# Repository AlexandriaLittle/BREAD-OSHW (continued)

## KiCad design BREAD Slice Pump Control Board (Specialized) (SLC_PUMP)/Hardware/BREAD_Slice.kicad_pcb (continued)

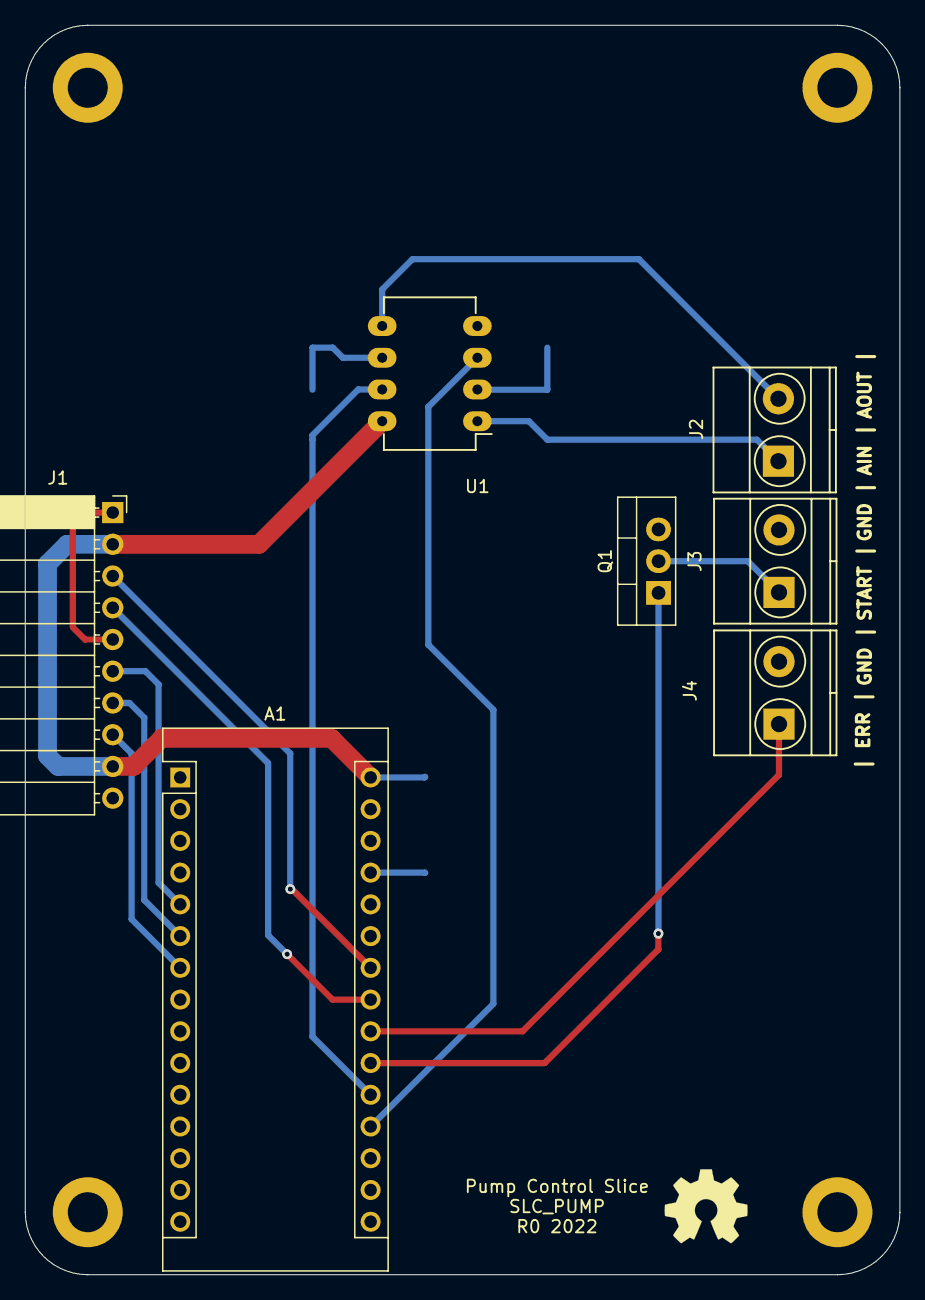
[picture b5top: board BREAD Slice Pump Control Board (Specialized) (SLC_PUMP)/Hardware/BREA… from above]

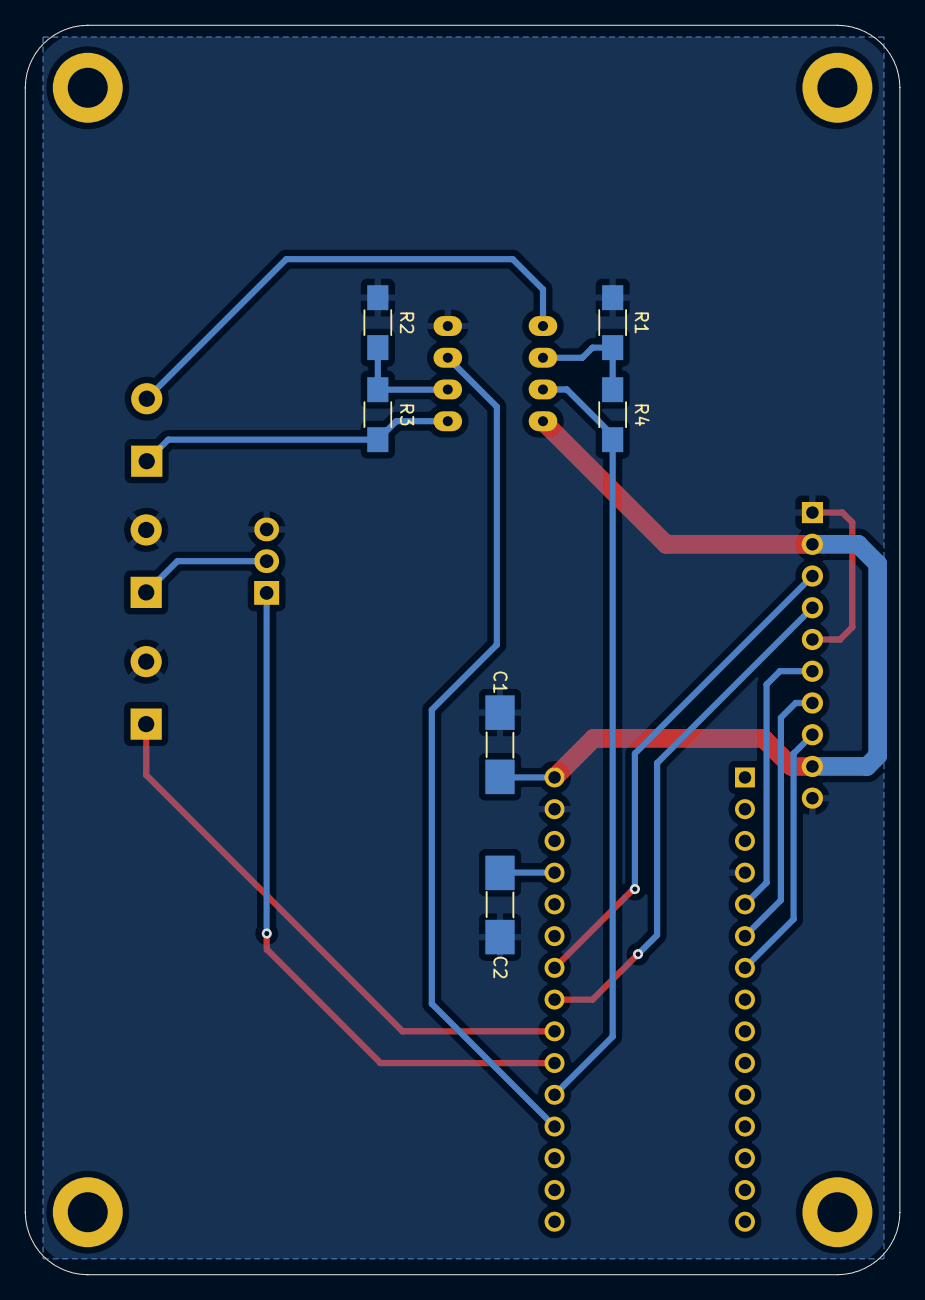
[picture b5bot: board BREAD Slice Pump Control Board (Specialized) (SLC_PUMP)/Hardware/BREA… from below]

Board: 2 copper layers, 70.0 x 100.0 mm, 18 parts (6 on the bottom side), 17 nets.

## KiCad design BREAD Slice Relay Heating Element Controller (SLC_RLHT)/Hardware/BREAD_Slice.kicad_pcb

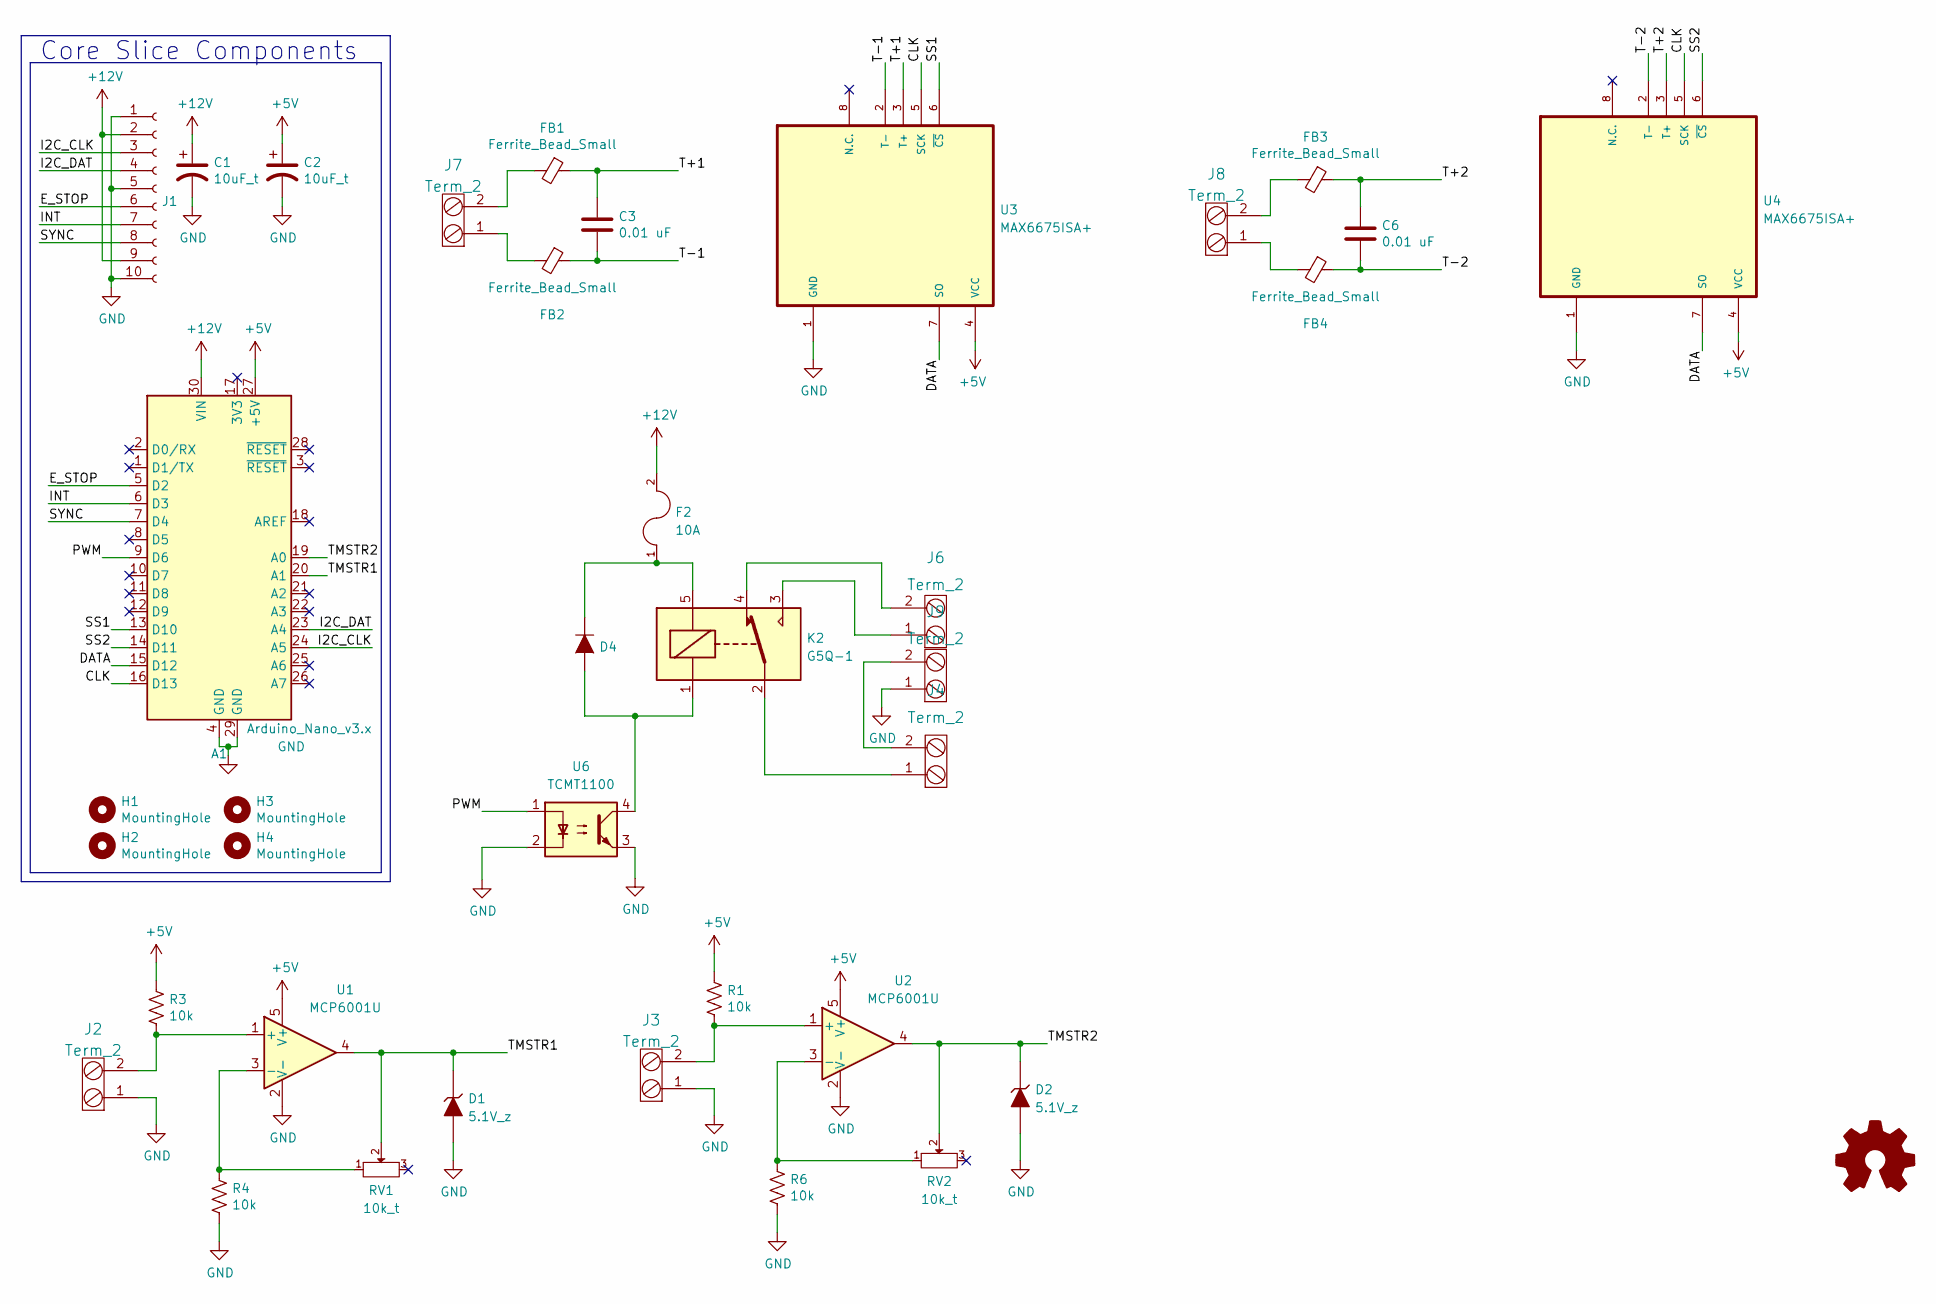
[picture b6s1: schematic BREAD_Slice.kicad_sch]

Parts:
A1: Arduino_Nano_v3.x; Arduino_Nano
C1, C2: 10uF_t; C_1206_3216Metric; Part # T491C106K025AT
C3, C6: 0.01 uF; C_1206_3216Metric
D1, D2: 5.1V_z; Diode_DO-41_SOD81_Horizontal_RM10; Part # 1N4733ATR
D4: General_Purpose_Diode; D_DO-201AD_P12.70mm_Horizontal; Part # 1N914BWS
F2: 10A; Fuse_Holder; Part # 3522-2
FB1, FB2, FB3, FB4: Ferrite_Bead_Small; R_1206_3216Metric
H1, H2, H3, H4: MountingHole; MountingHole_3.2mm_M3_DIN965_Pad
J1: Conn_01x10_Female; PinSocket_1x10_P2.54mm_Horizontal
J2, J3, J4, J6, J7, J8, J9: Term_2; TerminalBlock_Phoenix_MKDS-1,5-2_1x02_P5.00mm_Horizontal; Part # 1935161
K2: G5Q-1; Relay_SPDT_Omron-G5Q-1
Logo1: Logo_Open_Hardware_Small; OSHW-Symbol_6.7x6mm_SilkScreen
R1, R3, R4, R6: 10k; R_1206_HandSoldering
RV1, RV2: 10k_t; Potentiometer_Bourns_3296W_3-8Zoll_Inline_ScrewUp; Part # 1-1623849-0
U1, U2: MCP6001U; SOT-23-5
U3, U4: MAX6675ISA+; SOIC127P600X175-8N
U6: TCMT1100; SOP-4_4.4x2.6mm_P1.27mm

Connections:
+5V: A1.27 (+5V), C2.1, R1.1, R3.1, U1.5 (V+), U2.5 (V+), U3.4 (VCC), U4.4 (VCC)
+12V: A1.30 (VIN), C1.1, F2.2, J1.2, J1.9; also elsewhere on the board
/CLK: A1.16 (D13), U3.5 (SCK), U4.5 (SCK)
/DATA: A1.15 (D12), U3.7 (SO), U4.7 (SO)
/E_STOP: A1.5 (D2), J1.6
/I2C_CLK: A1.24 (A5), J1.3
/I2C_DAT: A1.23 (A4), J1.4
/INT: A1.6 (D3), J1.7
/PWM: A1.9 (D6), U6.1
/SS1: A1.13 (D10), U3.6 (~CS)
/SS2: A1.14 (D11), U4.6 (~CS)
/SYNC: A1.7 (D4), J1.8
/T+1: C3.1, FB1.1, U3.3 (T+)
/T+2: C6.1, FB3.1, U4.3 (T+)
/T-1: C3.2, FB2.1, U3.2 (T-)
/T-2: C6.2, FB4.1, U4.2 (T-)
/TMSTR1: A1.20 (A1), D1.1 (K), RV1.2, U1.4
/TMSTR2: A1.19 (A0), D2.1 (K), RV2.2, U2.4
GND: A1.4 (GND), A1.29 (GND), C1.2, C2.2, D1.2 (A), D2.2 (A), J1.1, J1.5, J1.10, J2.1, J3.1, J9.1, R4.2, R6.2, U1.2 (V-), U2.2 (V-), U3.1 (GND), U4.1 (GND), U6.2, U6.3
unnamed: D4.1 (K), F2.1, K2.5
unnamed: D4.2 (A), K2.1, U6.4
unnamed: FB1.2, J7.2
unnamed: FB2.2, J7.1
unnamed: FB3.2, J8.2
unnamed: FB4.2, J8.1
unnamed: J2.2, R3.2, U1.1 (+)
unnamed: J3.2, R1.2, U2.1 (+)
unnamed: J4.1, K2.2
unnamed: J6.1, K2.3
unnamed: J6.2, K2.4
unnamed: J4.2, J9.2
unnamed: R4.1, RV1.1, U1.3 (-)
unnamed: R6.1, RV2.1, U2.3 (-)

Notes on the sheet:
Core Slice Components

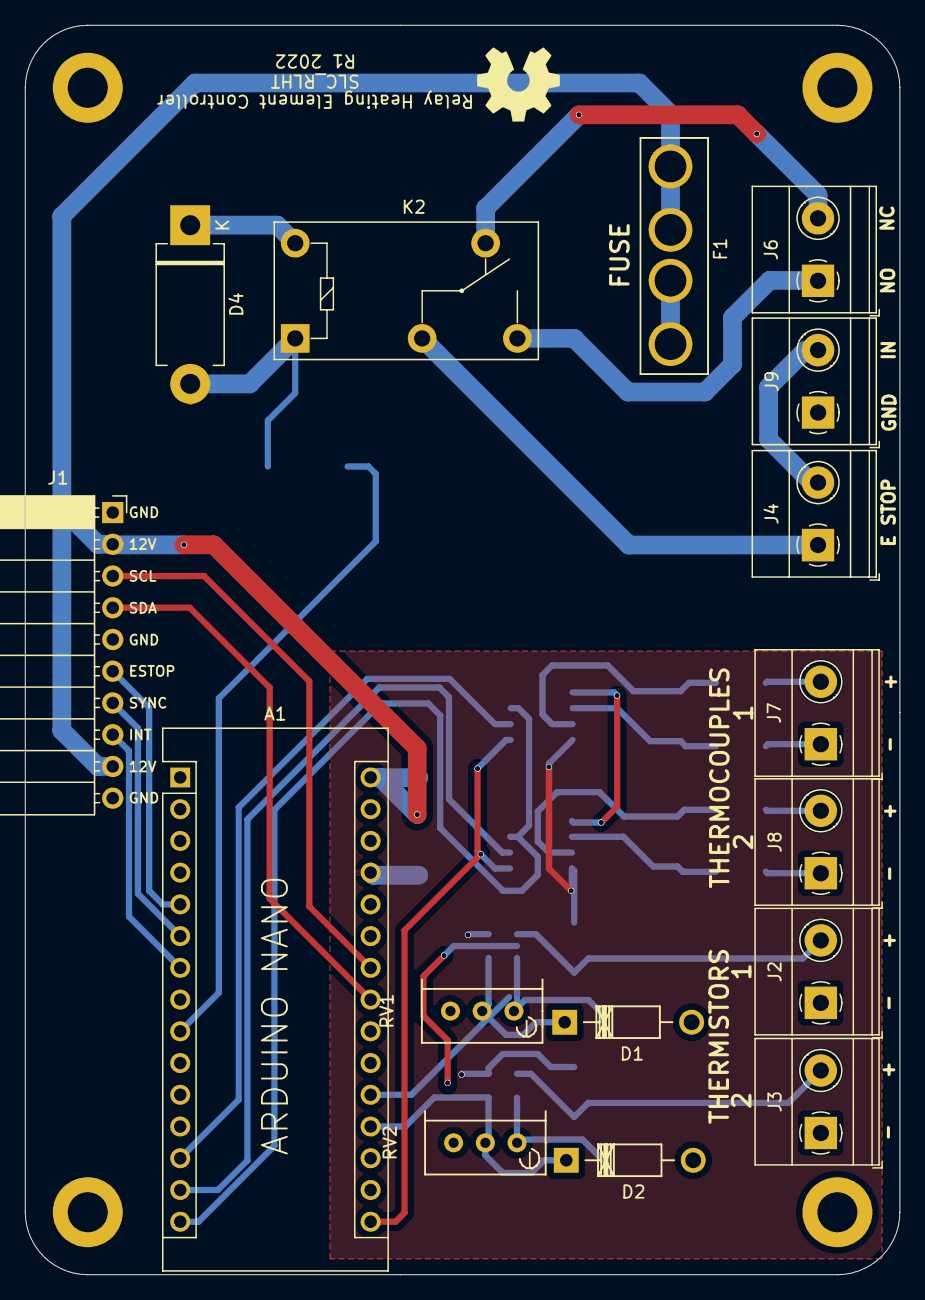
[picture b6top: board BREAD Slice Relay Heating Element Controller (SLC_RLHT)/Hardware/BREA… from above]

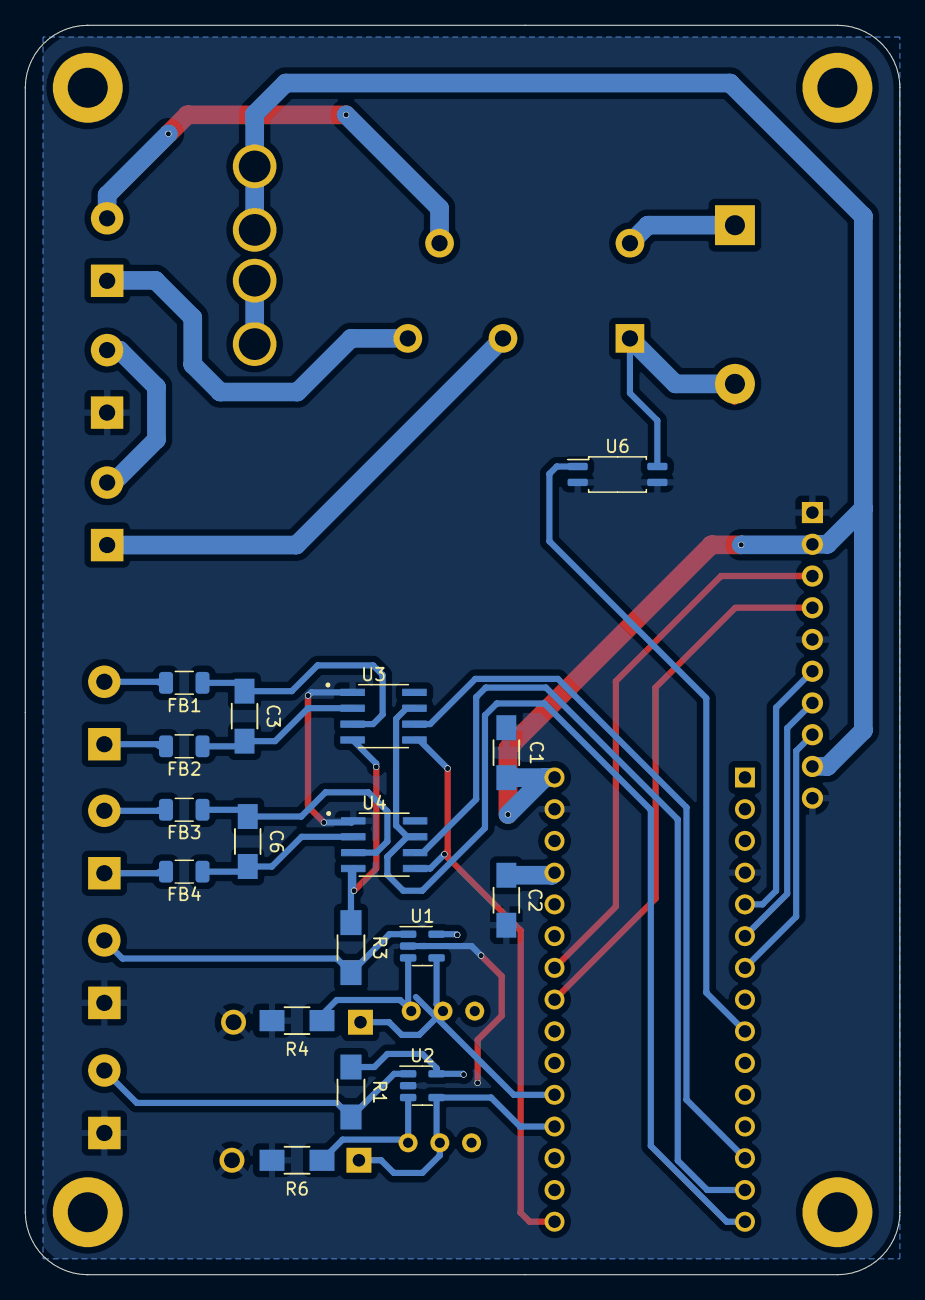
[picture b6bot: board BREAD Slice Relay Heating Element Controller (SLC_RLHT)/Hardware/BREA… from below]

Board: 2 copper layers, 70.0 x 100.0 mm, 38 parts (17 on the bottom side), 33 nets.

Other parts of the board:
F1: 10A; Fuse_Holder

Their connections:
+12V: F1.2; also elsewhere on the board

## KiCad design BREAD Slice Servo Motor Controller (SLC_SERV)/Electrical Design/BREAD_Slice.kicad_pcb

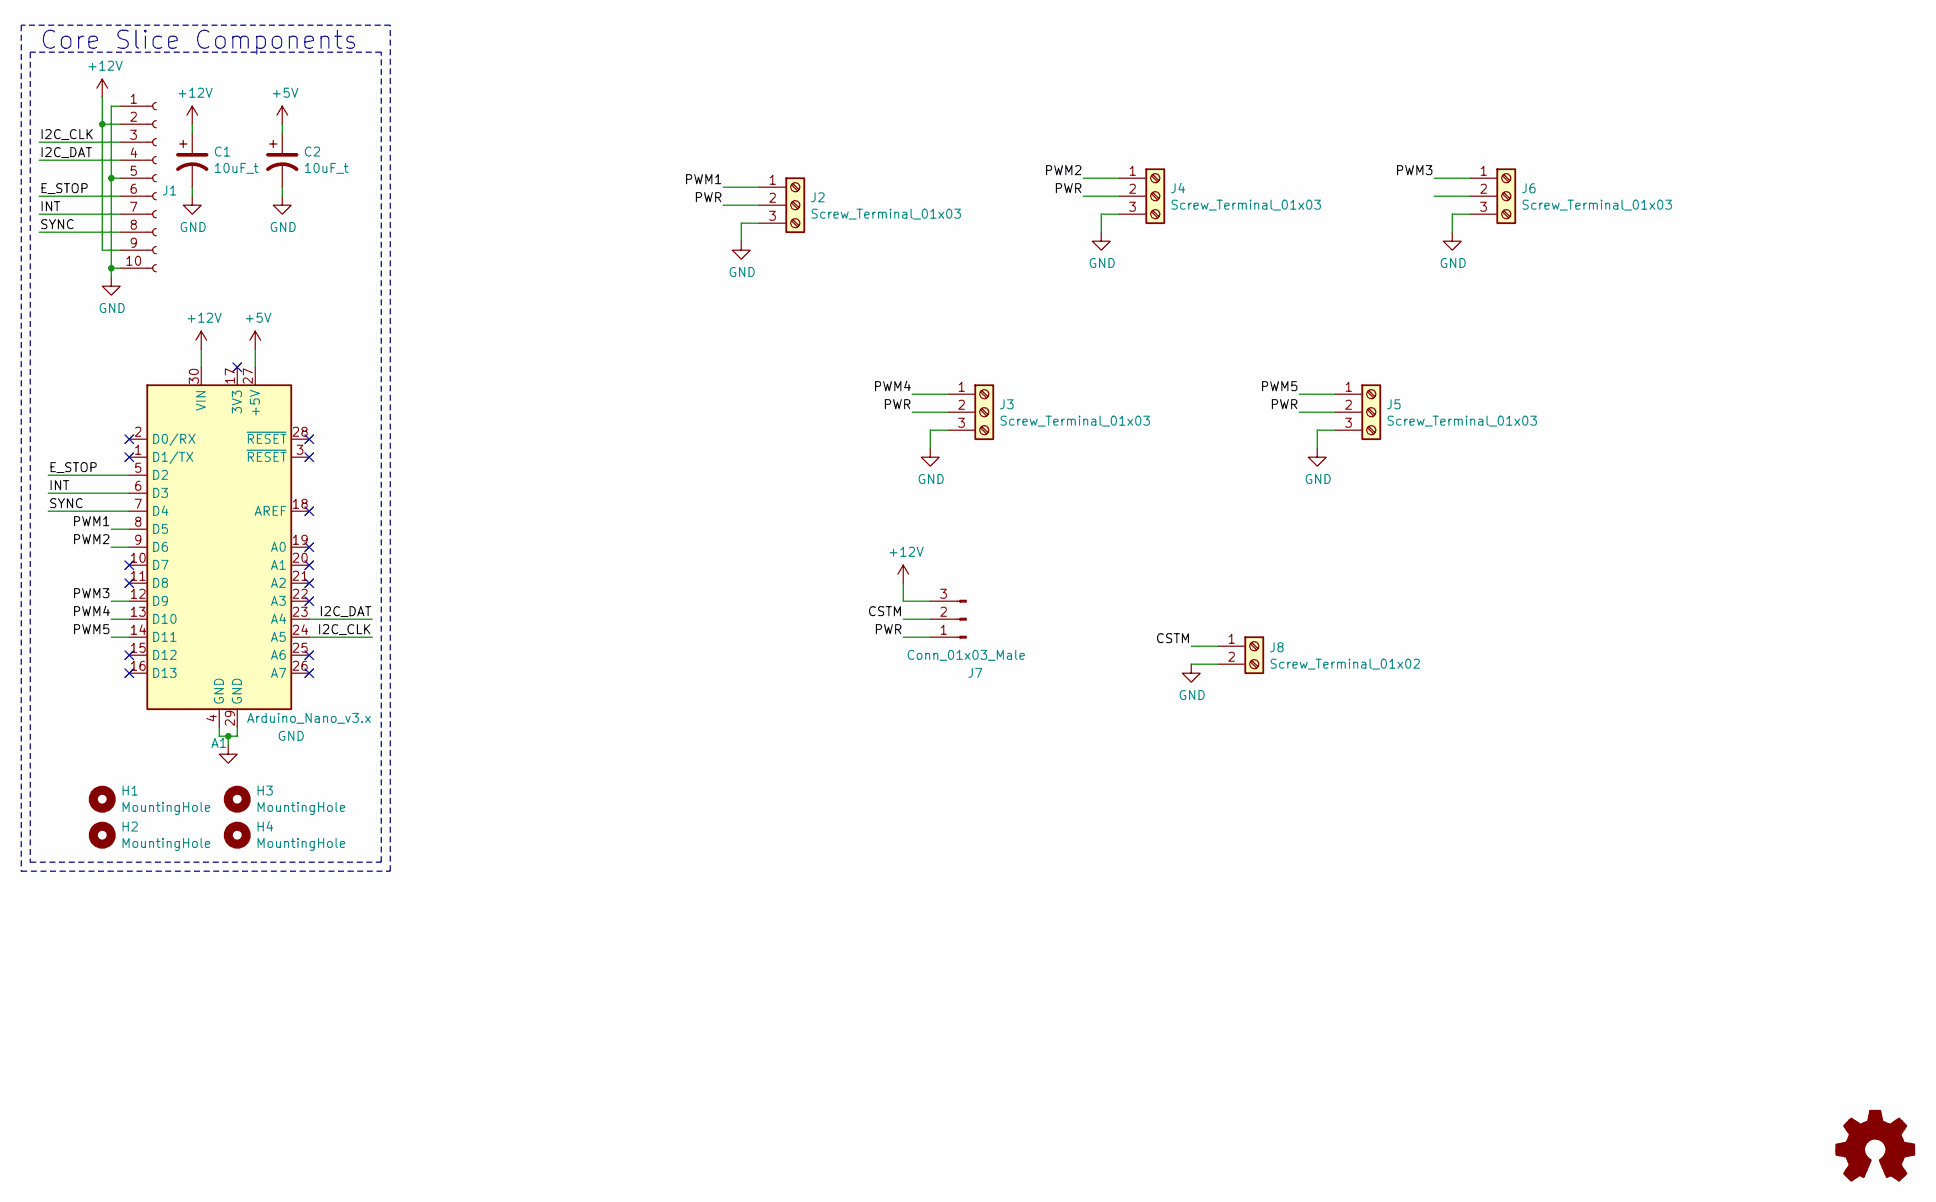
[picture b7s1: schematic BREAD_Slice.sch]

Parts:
A1: Arduino_Nano_v3.x; Arduino_Nano
C1, C2: 10uF_t; C_2312; Part # T491C106K025AT
H1, H2, H3, H4: MountingHole; MountingHole_3.2mm_M3_DIN965_Pad
J1: Conn_01x10_Female; PinSocket_1x10_P2.54mm_Horizontal
J2, J3, J4, J5, J6: Screw_Terminal_01x03; TerminalBlock_TE_282834-3_1x03_P2.54mm_Horizontal
J7: Conn_01x03_Male; PinSocket_1x03_P2.54mm_Vertical
J8: Screw_Terminal_01x02; TerminalBlock_TE_282834-2_1x02_P2.54mm_Horizontal
Logo1: Logo_Open_Hardware_Small; OSHW-Symbol_6.7x6mm_SilkScreen

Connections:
+5V: A1.27 (+5V), C2.1
+12V: A1.30 (VIN), C1.1, J1.2, J1.9, J7.3
/CSTM: J7.2, J8.1
/E_STOP: A1.5 (D2), J1.6
/I2C_CLK: A1.24 (A5), J1.3
/I2C_DAT: A1.23 (A4), J1.4
/INT: A1.6 (D3), J1.7
/PWM1: A1.8 (D5), J2.1
/PWM2: A1.9 (D6), J4.1
/PWM3: A1.12 (D9), J6.1
/PWM4: A1.13 (D10), J3.1
/PWM5: A1.14 (D11), J5.1
/PWR: J2.2, J3.2, J4.2, J5.2, J7.1
/SYNC: A1.7 (D4), J1.8
GND: A1.4 (GND), A1.29 (GND), C1.2, C2.2, J1.1, J1.5, J1.10, J2.3, J3.3, J4.3, J5.3, J6.3, J8.2

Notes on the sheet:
Core Slice Components

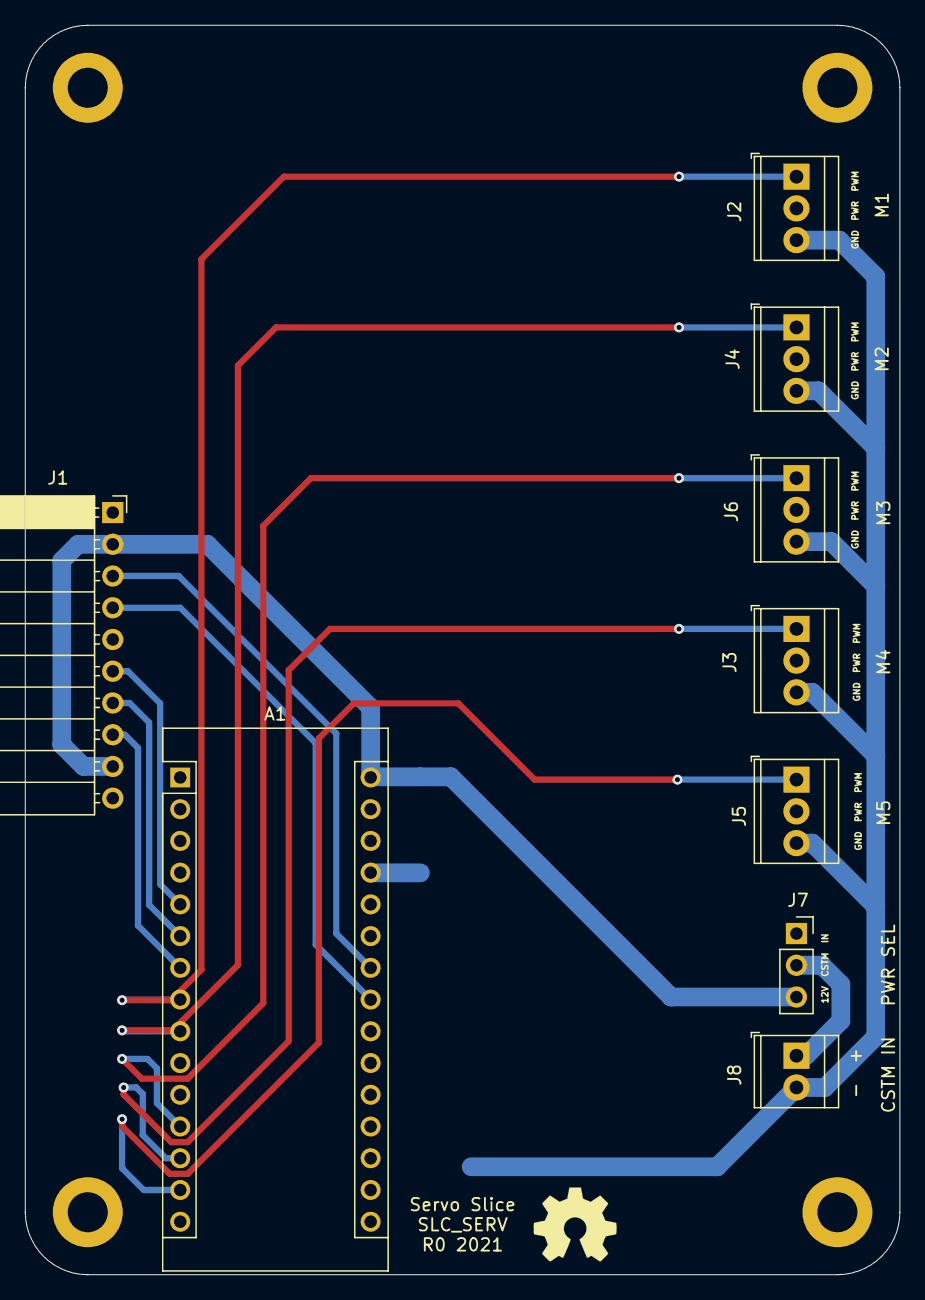
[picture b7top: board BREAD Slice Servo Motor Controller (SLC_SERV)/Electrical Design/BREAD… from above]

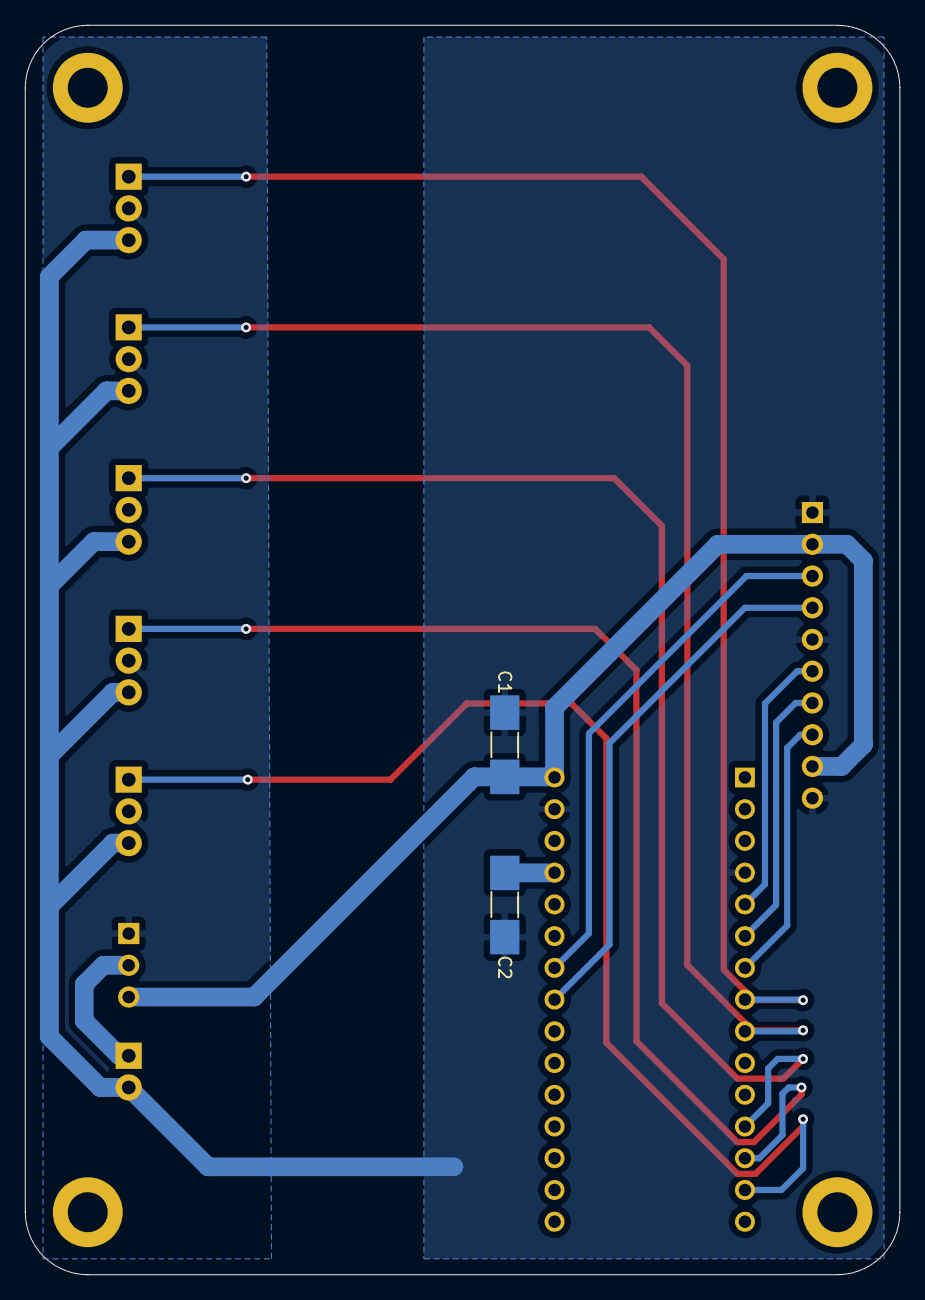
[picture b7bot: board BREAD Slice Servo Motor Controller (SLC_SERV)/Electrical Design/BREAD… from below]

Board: 2 copper layers, 70.0 x 100.0 mm, 16 parts (2 on the bottom side), 15 nets.

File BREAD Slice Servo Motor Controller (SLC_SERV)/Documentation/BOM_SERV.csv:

"Id";"Designator";"Package";"Quantity";"Designation";"Supplier and ref";
1;"J8";"TerminalBlock_TE_282834-2_1x02_P2.54mm_Horizontal";1;"Screw_Terminal_01x02";;;
2;"J7";"PinSocket_1x03_P2.54mm_Vertical";1;"Conn_01x03_Male";;;
3;"J6,J5,J4,J3,J2";"TerminalBlock_TE_282834-3_1x03_P2.54mm_Horizontal";5;"Screw_Terminal_01x03";;;
4;"Logo1";"OSHW-Symbol_6.7x6mm_SilkScreen";1;"Logo_Open_Hardware_Small";;;
5;"H4,H3,H2,H1";"MountingHole_3.2mm_M3_DIN965_Pad";4;"MountingHole";;;
6;"C1,C2";"C_2312";2;"10uF_t";;;
7;"A1";"Arduino_Nano";1;"Arduino_Nano_v3.x";;;
8;"J1";"PinSocket_1x10_P2.54mm_Horizontal";1;"Conn_01x10_Female";;;
